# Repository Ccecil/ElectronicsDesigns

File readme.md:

"Just Another UART"

UART<>USB device based on the Silicon Labs CP2104

This project was made mostly as practice but to also supply developers/users of Smoothieboard V2 with a common UART<>USB device to help "standardize" testing and setup.

Designed in Kicad 6

It is to be considered a work in process.

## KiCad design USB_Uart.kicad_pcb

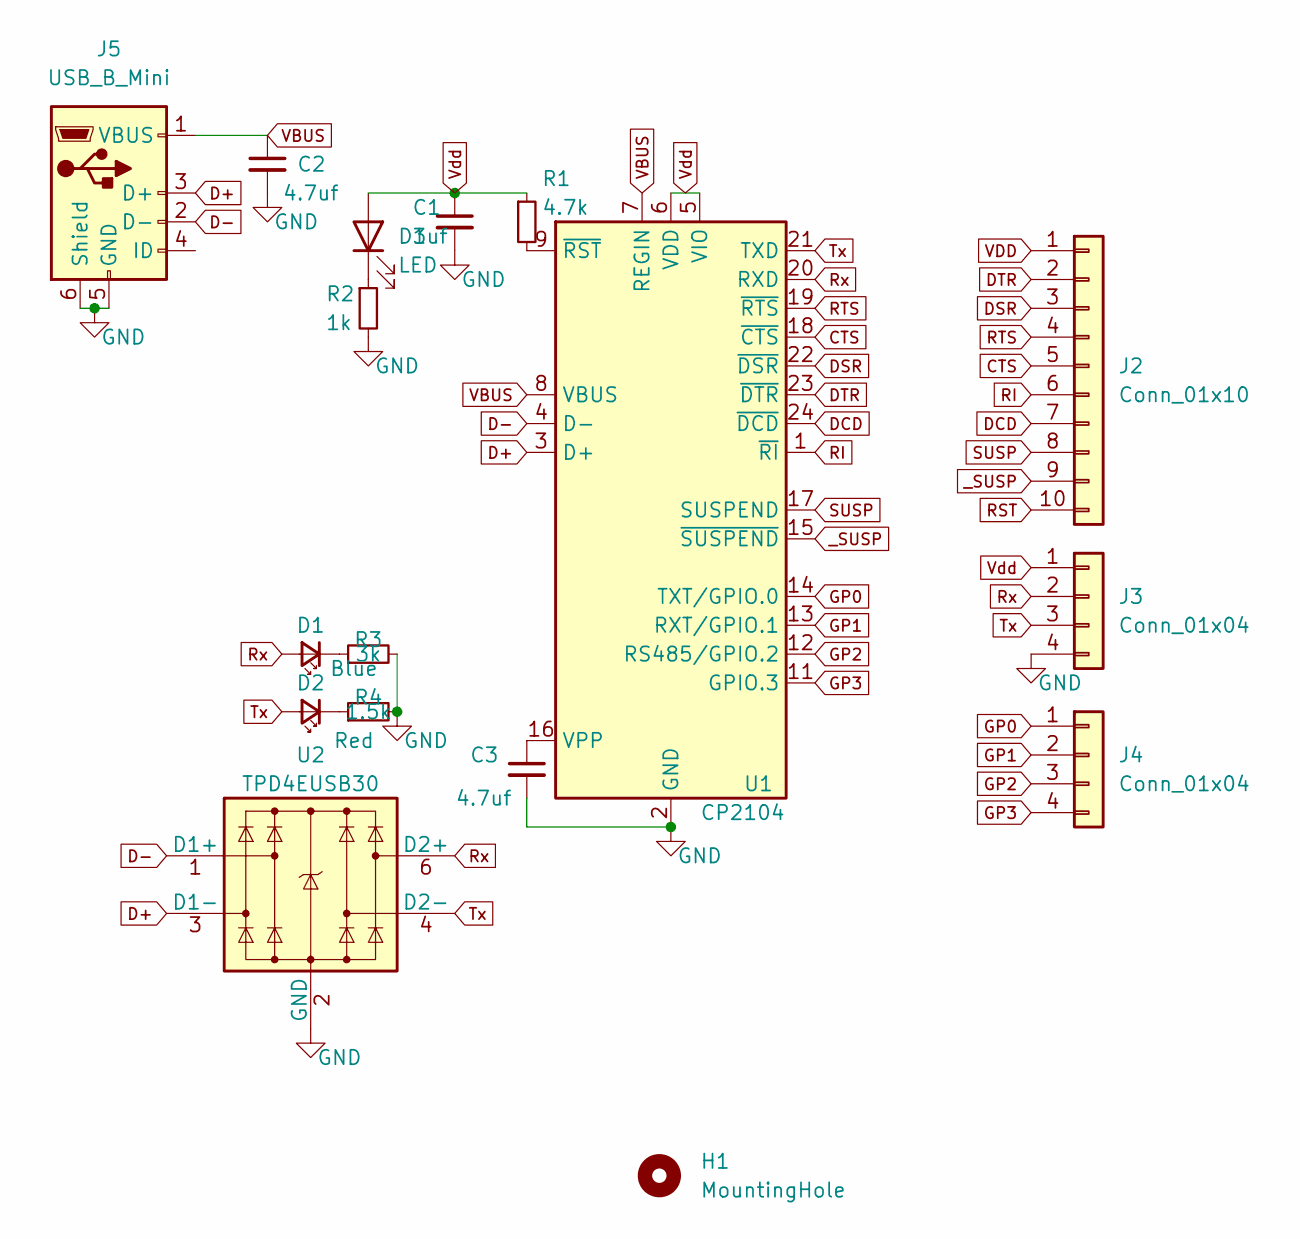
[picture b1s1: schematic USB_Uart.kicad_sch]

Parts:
C1: 1uf; C_0402_1005Metric
C2, C3: 4.7uf; C_0402_1005Metric
D1: Blue; LED_0603_1608Metric
D2: Red; LED_0603_1608Metric
D3: LED; LED_0603_1608Metric
H1: MountingHole
J2: Conn_01x10; PinHeader_1x10_P2.54mm_Vertical
J3: Conn_01x04; Molex_KK-254_AE-6410-04A_1x04_P2.54mm_Vertical
J4: Conn_01x04; PinHeader_1x04_P2.54mm_Vertical
J5: USB_B_Mini; USB_Micro-B_Molex-105017-0001
R1: 4.7k; R_0402_1005Metric
R2: 1k; R_0402_1005Metric
R3: 3k; R_0402_1005Metric
R4: 1.5k; R_0402_1005Metric
U1: CP2104; QFN-24-1EP_4x4mm_P0.5mm_EP2.6x2.6mm
U2: TPD4EUSB30; SOT-363_SC-70-6

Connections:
CTS: J2.5, U1.18 (~CTS)
D+: J5.3 (D+), U1.3 (D+), U2.3 (D1-)
D-: J5.2 (D-), U1.4 (D-), U2.1 (D1+)
DCD: J2.7, U1.24 (~DCD)
DSR: J2.3, U1.22 (~DSR)
DTR: J2.2, U1.23 (~DTR)
GND: C1.2, C2.2, C3.2, J3.4, J5.5 (GND), J5.6 (Shield), R2.2, R3.2, R4.2, U1.2 (GND), U1.25 (GND), U2.2 (GND)
GP0: J4.1, U1.14 (TXT/GPIO.0)
GP1: J4.2, U1.13 (RXT/GPIO.1)
GP2: J4.3, U1.12 (RS485/GPIO.2)
GP3: J4.4, U1.11 (GPIO.3)
unnamed: C3.1, U1.16 (VPP)
unnamed: D1.1 (K), R3.1
unnamed: D2.1 (K), R4.1
unnamed: D3.1 (K), R2.1
unnamed: R1.2, U1.9 (~RST)
RI: J2.6, U1.1 (~RI)
RST: J2.10
RTS: J2.4, U1.19 (~RTS)
Rx: D1.2 (A), J3.2, U1.20 (RXD), U2.6 (D2+)
SUSP: J2.8, U1.17 (SUSPEND)
Tx: D2.2 (A), J3.3, U1.21 (TXD), U2.4 (D2-)
VBUS: C2.1, J5.1 (VBUS), U1.7 (REGIN), U1.8 (VBUS)
Vdd: C1.1, D3.2 (A), J2.1, J3.1, R1.1, U1.5 (VIO), U1.6 (VDD)
_SUSP: J2.9, U1.15 (~SUSPEND)

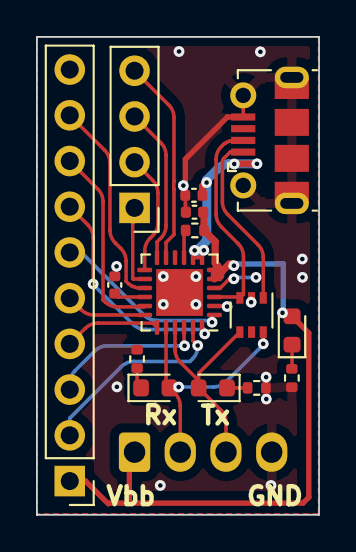
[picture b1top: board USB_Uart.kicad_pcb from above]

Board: 2 copper layers, 15.7 x 26.5 mm, 16 parts (1 on the bottom side), 24 nets.

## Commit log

2021-12-18 Initial upload
    Basic files and schematic.
2021-12-20 Update Schematic, start footprint layout
2021-12-21 Layout footprints, Adjust schematic
2021-12-23 Switch to USB-B-Micro, add routing
2022-01-03 Fix Layout, fill zones.
2022-01-03 Fine tuning traces and fills. Added Silkscreen
2022-01-03 First round DRC
2023-05-27 Update files, add BOM and JPG
